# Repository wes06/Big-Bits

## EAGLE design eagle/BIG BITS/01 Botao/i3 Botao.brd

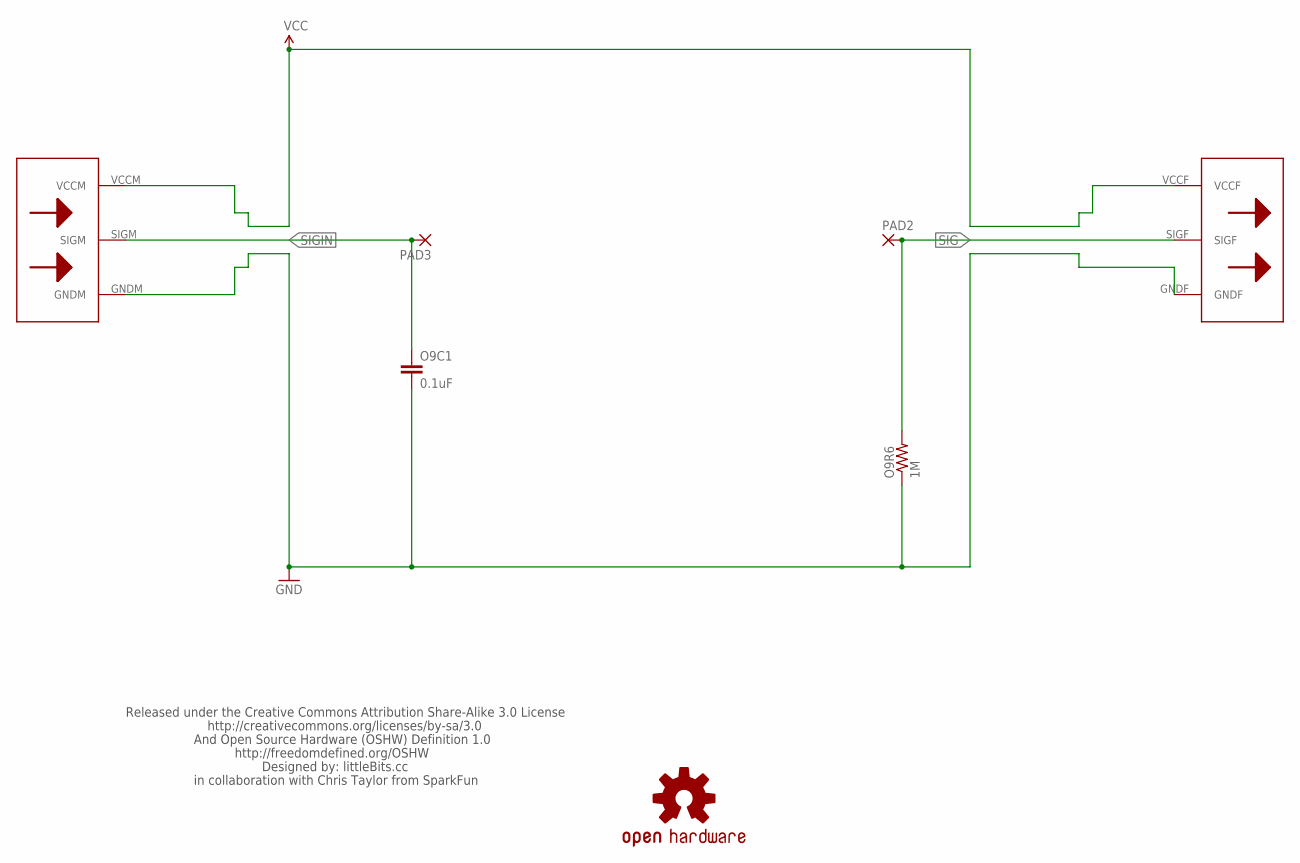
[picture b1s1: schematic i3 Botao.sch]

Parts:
O9C1: 0.1uF; 1206
O9R6: 1M; 0805
PAD2, PAD3: SMD5; SMD2,54-5,08
U$1: LB_CREDITS; OSHWCREDIT
U$2: BIGBIT
U$3: OSHW-LOGOL; OSHW-LOGO-L

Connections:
GND: O9C1.2, O9R6.1, U$2.GNDF, U$2.GNDM
SIG: O9R6.2, PAD2.1, U$2.SIGF
SIGIN: O9C1.1, PAD3.1, U$2.SIGM
VCC: U$2.VCCF, U$2.VCCM

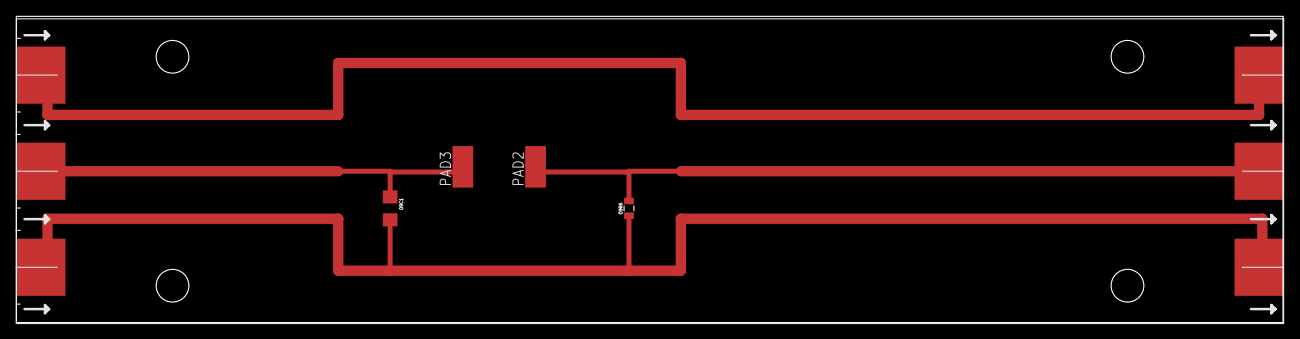
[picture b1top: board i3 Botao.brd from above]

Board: 2 copper layers, 154.9 x 37.5 mm, 7 parts (0 on the bottom side), 4 nets.

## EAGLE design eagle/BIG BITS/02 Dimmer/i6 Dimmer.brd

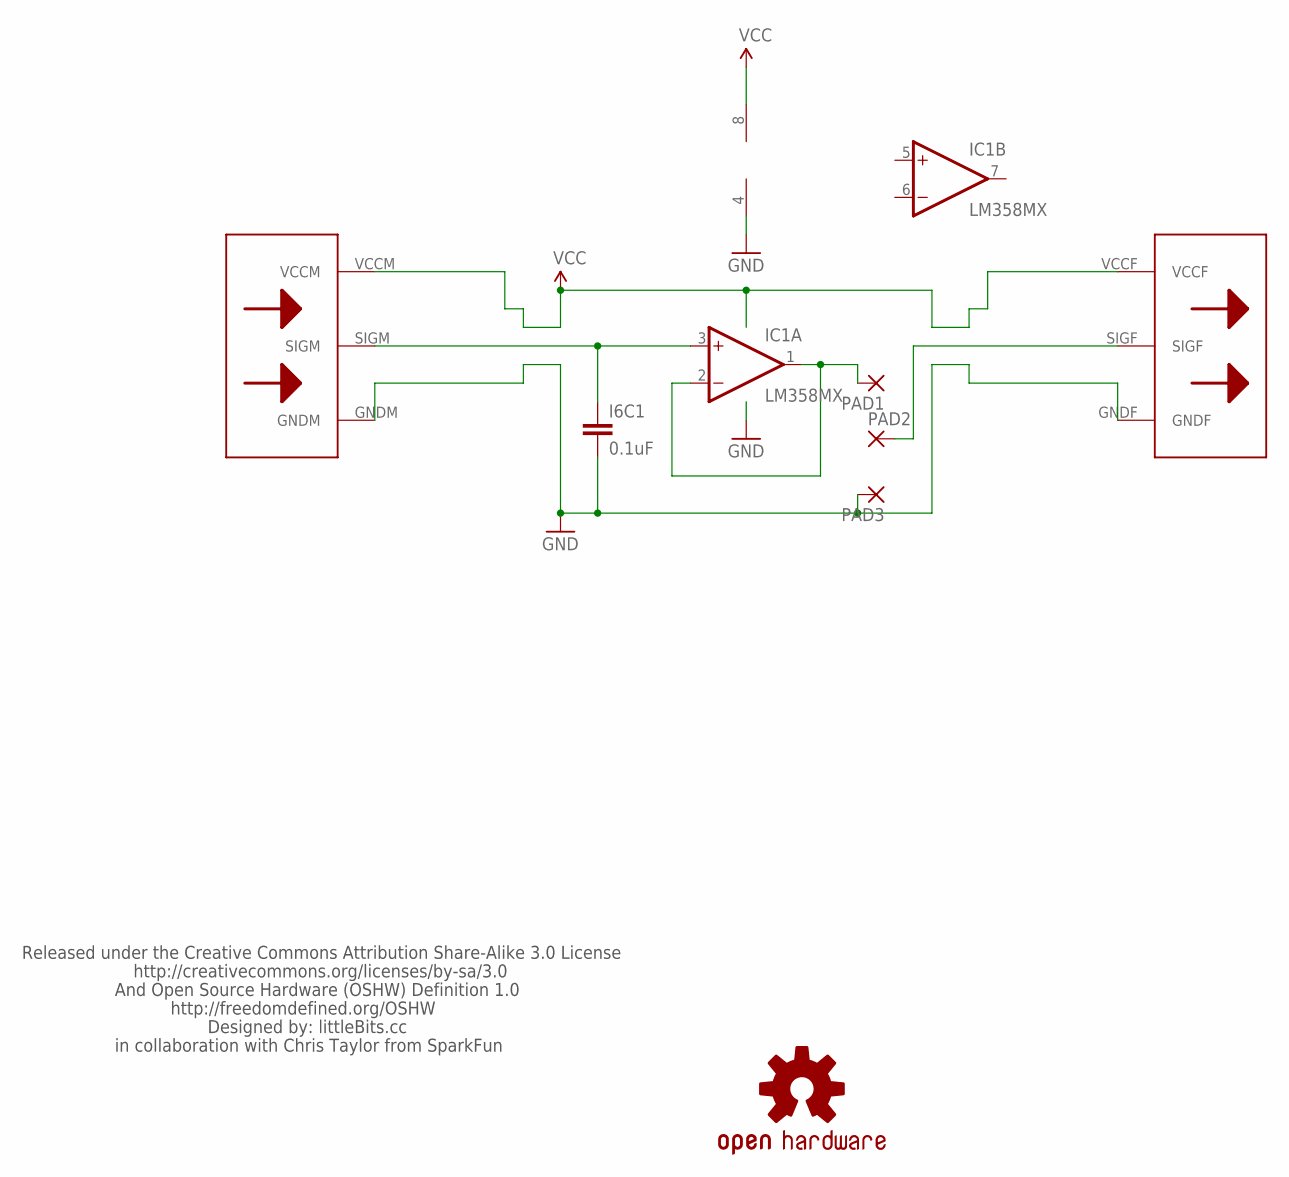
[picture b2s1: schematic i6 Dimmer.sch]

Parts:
I6C1: 0.1uF; 1206
IC1: LM358MX; SO08
PAD1, PAD2, PAD3: SMD5; SMD2,54-5,08
U$1: LB_CREDITS; OSHWCREDIT
U$3: OSHW-LOGOL; OSHW-LOGO-L
U$6: BIGBIT

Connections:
GND: I6C1.2, IC1.4 (V-), PAD3.1, U$6.GNDF, U$6.GNDM
unnamed: IC1.1 (OUT), IC1.2 (-IN), PAD1.1
POT: PAD2.1, U$6.SIGF
SIG: I6C1.1, IC1.3 (+IN), U$6.SIGM
VCC: IC1.8 (V+), U$6.VCCF, U$6.VCCM

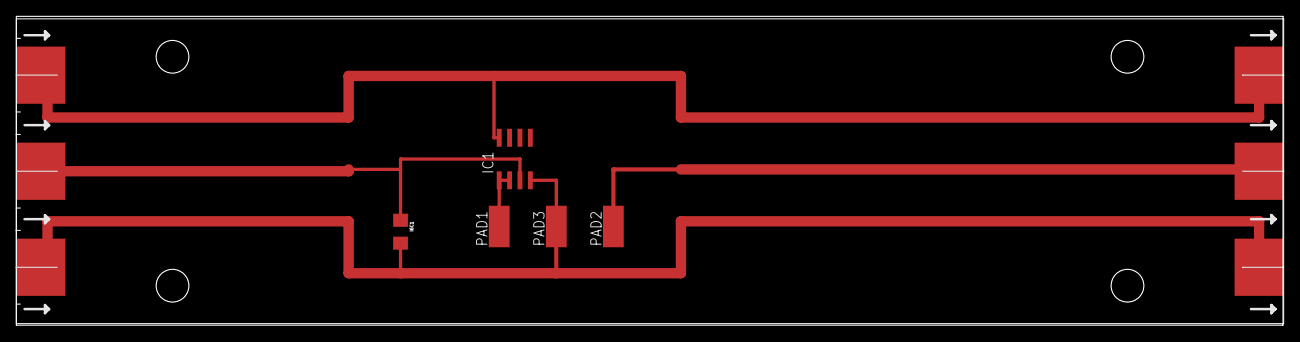
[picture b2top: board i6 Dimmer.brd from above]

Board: 2 copper layers, 154.9 x 37.8 mm, 8 parts (0 on the bottom side), 5 nets.

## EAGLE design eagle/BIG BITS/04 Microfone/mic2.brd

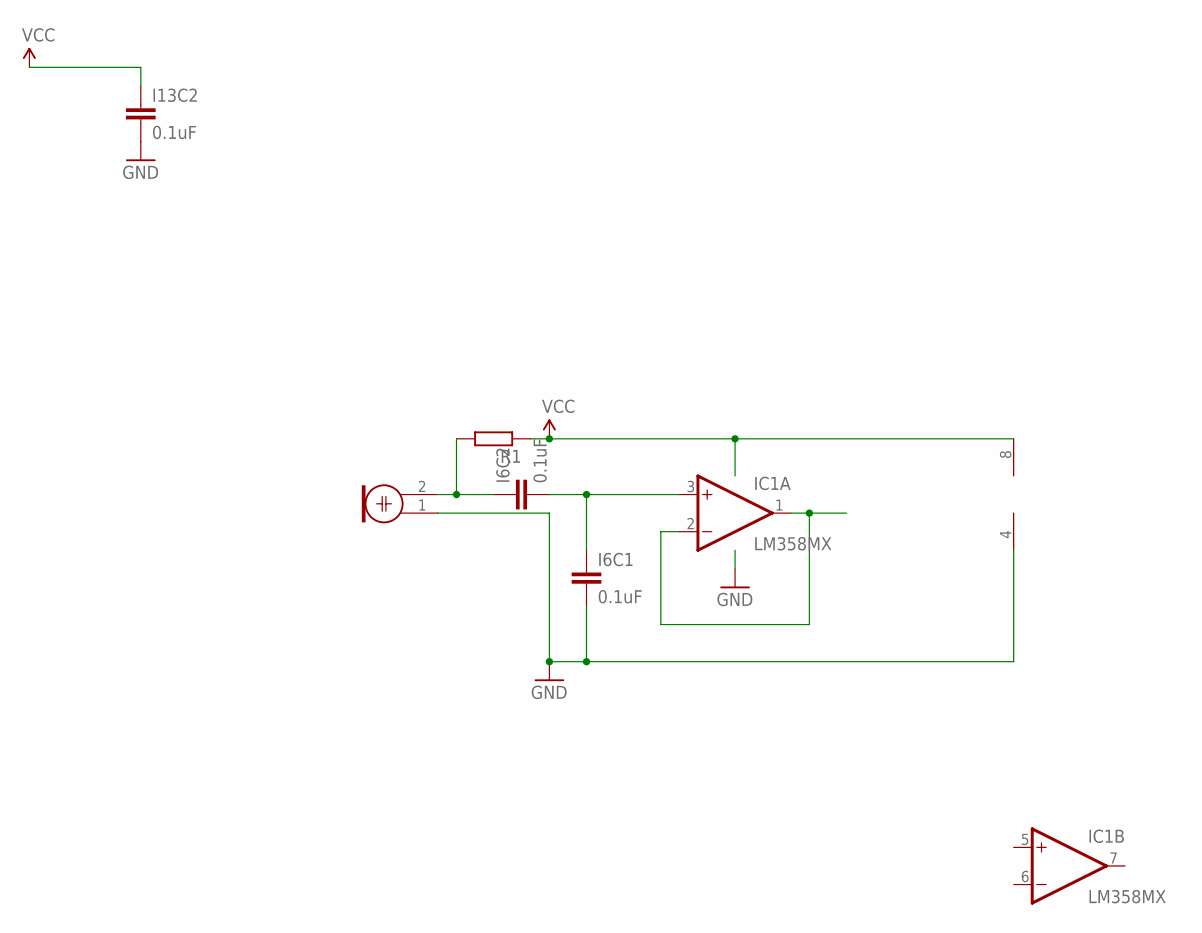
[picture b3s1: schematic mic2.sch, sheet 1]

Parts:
I6C1, I6C2, I13C2: 0.1uF; 1206
IC1: LM358MX; SO08
M1: ELECTRET_MICROPHON-WM-61A; WM-61A
R1: R-EU_M0805; M0805

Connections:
BLA: I6C1.1, I6C2.2, IC1.3 (+IN)
GND: I6C1.2, I13C2.2, IC1.4 (V-), M1.1; also elsewhere on the board
unnamed: I6C2.1, M1.2, R1.2
SIG: IC1.1 (OUT), IC1.2 (-IN)
VCC: I13C2.1, IC1.8 (V+), R1.1; also elsewhere on the board

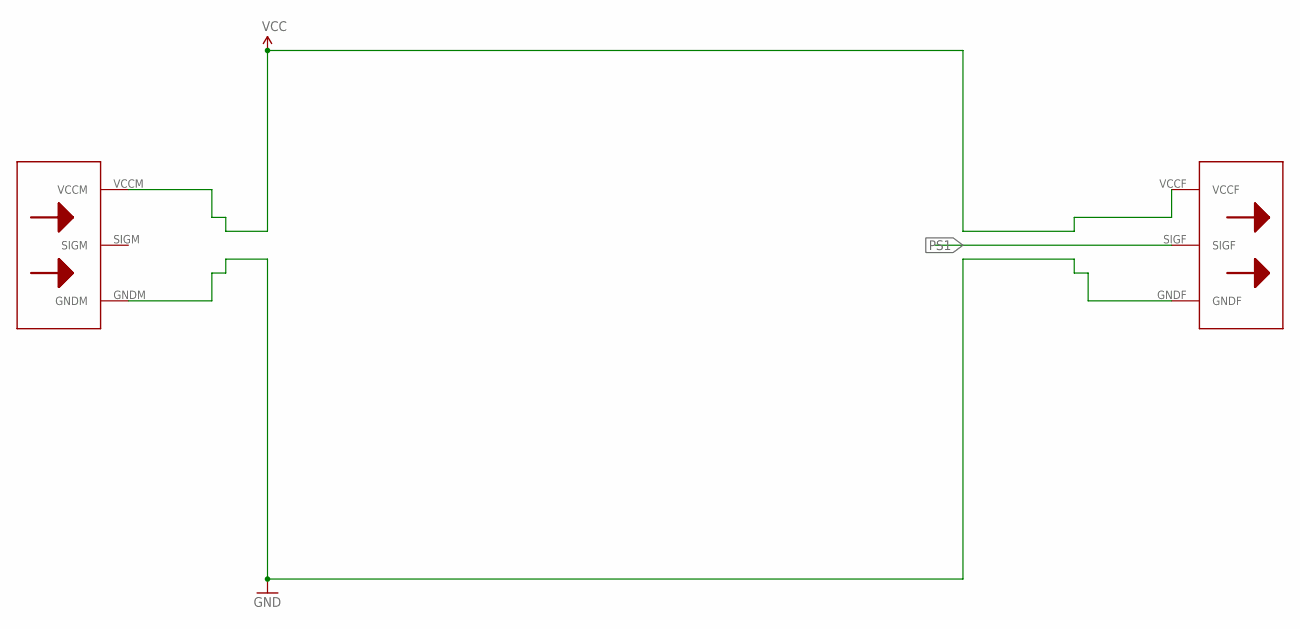
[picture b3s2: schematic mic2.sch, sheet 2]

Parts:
U$3: BIGBIT

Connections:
GND: U$3.GNDF, U$3.GNDM; also elsewhere on the board
PS1: U$3.SIGF
VCC: U$3.VCCF, U$3.VCCM; also elsewhere on the board

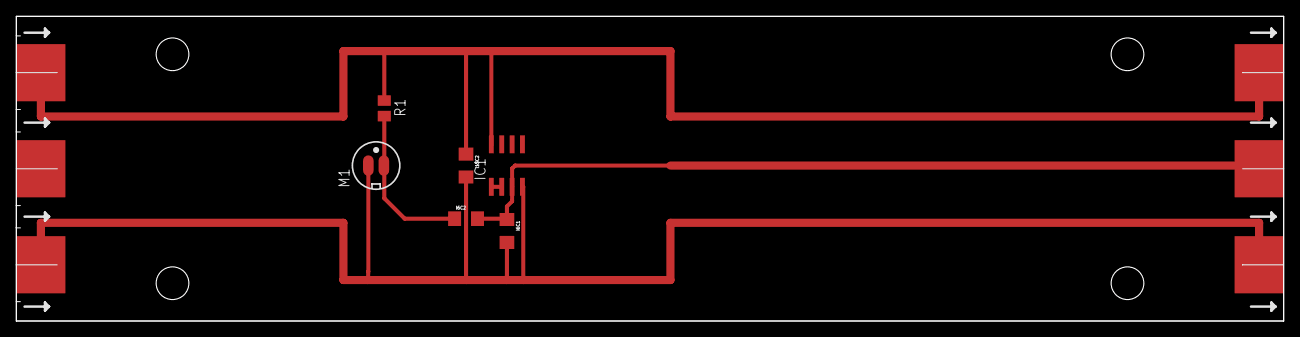
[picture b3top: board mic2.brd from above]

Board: 2 copper layers, 155.0 x 37.2 mm, 7 parts (0 on the bottom side), 5 nets.

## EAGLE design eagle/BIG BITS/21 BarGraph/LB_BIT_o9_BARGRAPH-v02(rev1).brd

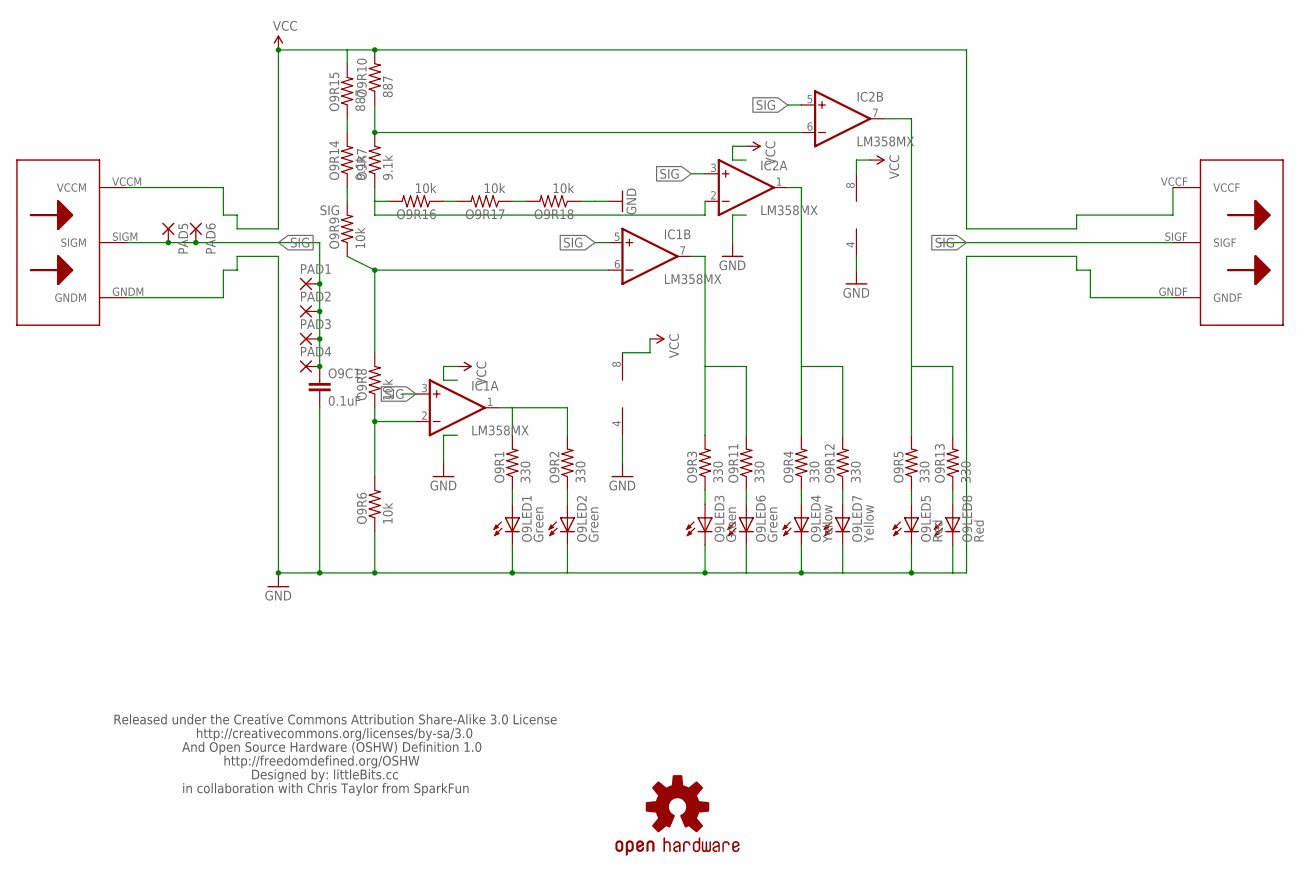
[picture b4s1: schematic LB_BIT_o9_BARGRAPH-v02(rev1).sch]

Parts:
IC1, IC2: LM358MX; SO08
O9C1: 0.1uF; 0603-CAP
O9LED1, O9LED2, O9LED3, O9LED6: Green; LED-1206
O9LED4, O9LED7: Yellow; LED-1206
O9LED5, O9LED8: Red; LED-1206
O9R1, O9R2, O9R3, O9R4, O9R5, O9R11, O9R12, O9R13: 330; 0805
O9R6, O9R8, O9R9, O9R16, O9R17, O9R18: 10k; 0805
O9R7, O9R14: 9.1k; 0805
O9R10, O9R15: 887; 0805
PAD1, PAD2, PAD3, PAD4, PAD5, PAD6: SMD2; SMD1,27-2,54
U$1: LB_CREDITS; OSHWCREDIT
U$3: OSHW-LOGOL; OSHW-LOGO-L
U$7: BIGBIT

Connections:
GND: IC1.4 (V-), IC2.4 (V-), O9C1.2, O9LED1.C, O9LED2.C, O9LED3.C, O9LED4.C, O9LED5.C, O9LED6.C, O9LED7.C, O9LED8.C, O9R6.1, O9R18.1, U$7.GNDF, U$7.GNDM
unnamed: IC1.1 (OUT), O9R1.2, O9R2.2
unnamed: O9LED1.A, O9R1.1
unnamed: O9R14.2, O9R15.1
unnamed: O9LED3.A, O9R3.1
unnamed: O9LED4.A, O9R4.1
unnamed: O9LED5.A, O9R5.1
unnamed: O9LED8.A, O9R13.1
unnamed: O9R9.2, O9R14.1
unnamed: O9LED7.A, O9R12.1
unnamed: O9LED6.A, O9R11.1
unnamed: IC1.7 (OUT), O9R3.2, O9R11.2
unnamed: IC2.1 (OUT), O9R4.2, O9R12.2
unnamed: IC2.7 (OUT), O9R5.2, O9R13.2
unnamed: IC1.2 (-IN), O9R6.2, O9R8.1
unnamed: IC2.2 (-IN), O9R7.1, O9R16.2
unnamed: IC1.6 (-IN), O9R8.2, O9R9.1
unnamed: O9R16.1, O9R17.2
unnamed: O9R17.1, O9R18.2
unnamed: O9LED2.A, O9R2.1
unnamed: IC2.6 (-IN), O9R7.2, O9R10.1
SIG: IC1.3 (+IN), IC1.5 (+IN), IC2.3 (+IN), IC2.5 (+IN), O9C1.1, PAD1.1, PAD2.1, PAD3.1, PAD4.1, PAD5.1, PAD6.1, U$7.SIGF, U$7.SIGM
VCC: IC1.8 (V+), IC2.8 (V+), O9R10.2, O9R15.2, U$7.VCCF, U$7.VCCM

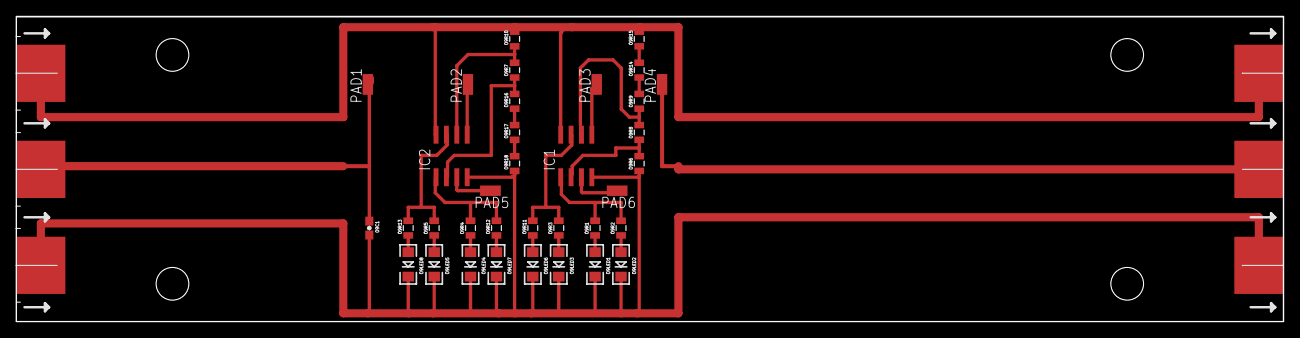
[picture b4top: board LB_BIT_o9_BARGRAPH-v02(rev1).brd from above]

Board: 2 copper layers, 155.0 x 37.3 mm, 38 parts (0 on the bottom side), 23 nets.

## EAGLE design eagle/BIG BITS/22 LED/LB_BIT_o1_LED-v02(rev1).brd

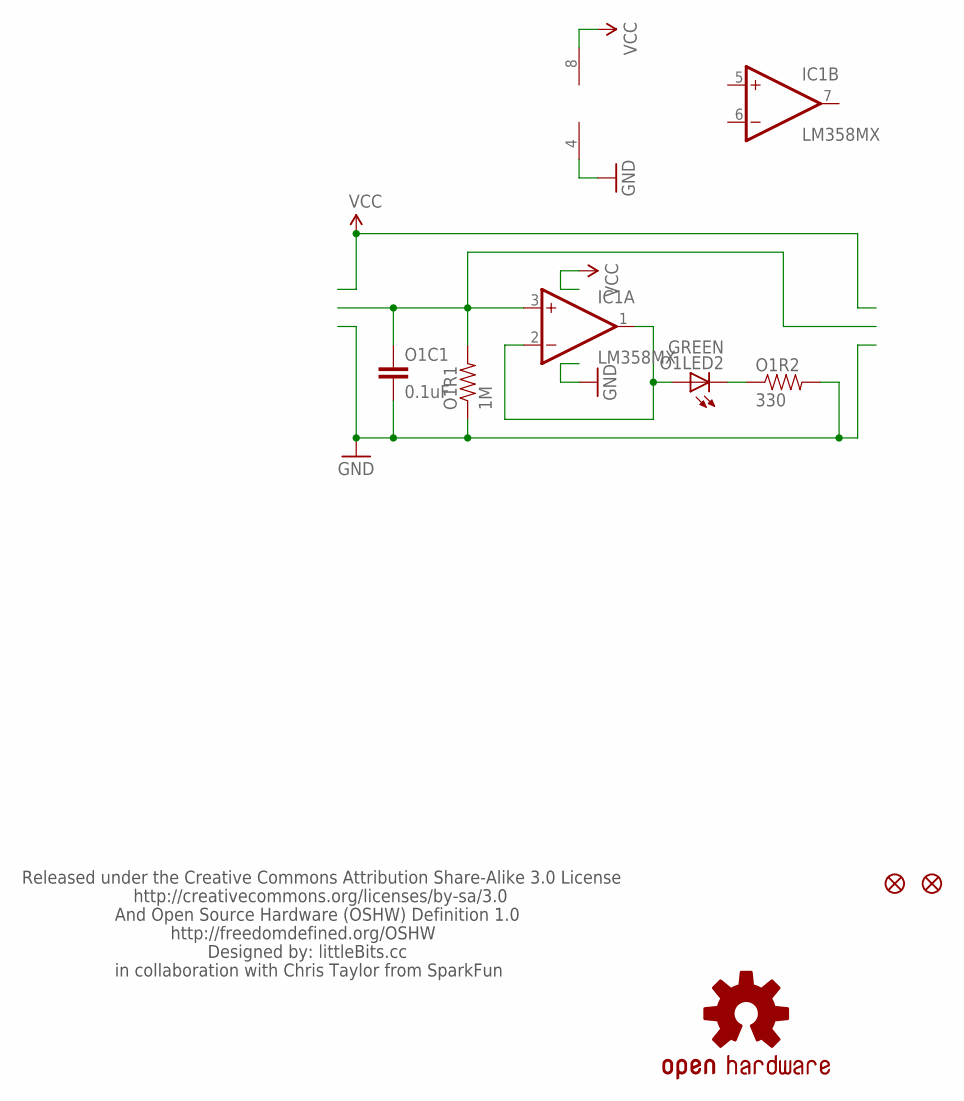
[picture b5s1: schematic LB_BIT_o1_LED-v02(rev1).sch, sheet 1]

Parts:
IC1: LM358MX; SO08
JP1, JP2: FIDUCIAL1X2.5; FIDUCIAL-1X2.5
O1C1: 0.1uF; 1206
O1LED2: GREEN; LED-1206
O1R1: 1M; 0805
O1R2: 330; 0805
U$1: LB_CREDITS; OSHWCREDIT
U$3: OSHW-LOGOL; OSHW-LOGO-L

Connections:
GND: IC1.4 (V-), O1C1.2, O1R1.1, O1R2.2; also elsewhere on the board
LEDGND: O1LED2.C, O1R2.1
unnamed: IC1.1 (OUT), IC1.2 (-IN), O1LED2.A
SIG: IC1.3 (+IN), O1C1.1, O1R1.2; also elsewhere on the board
VCC: IC1.8 (V+); also elsewhere on the board

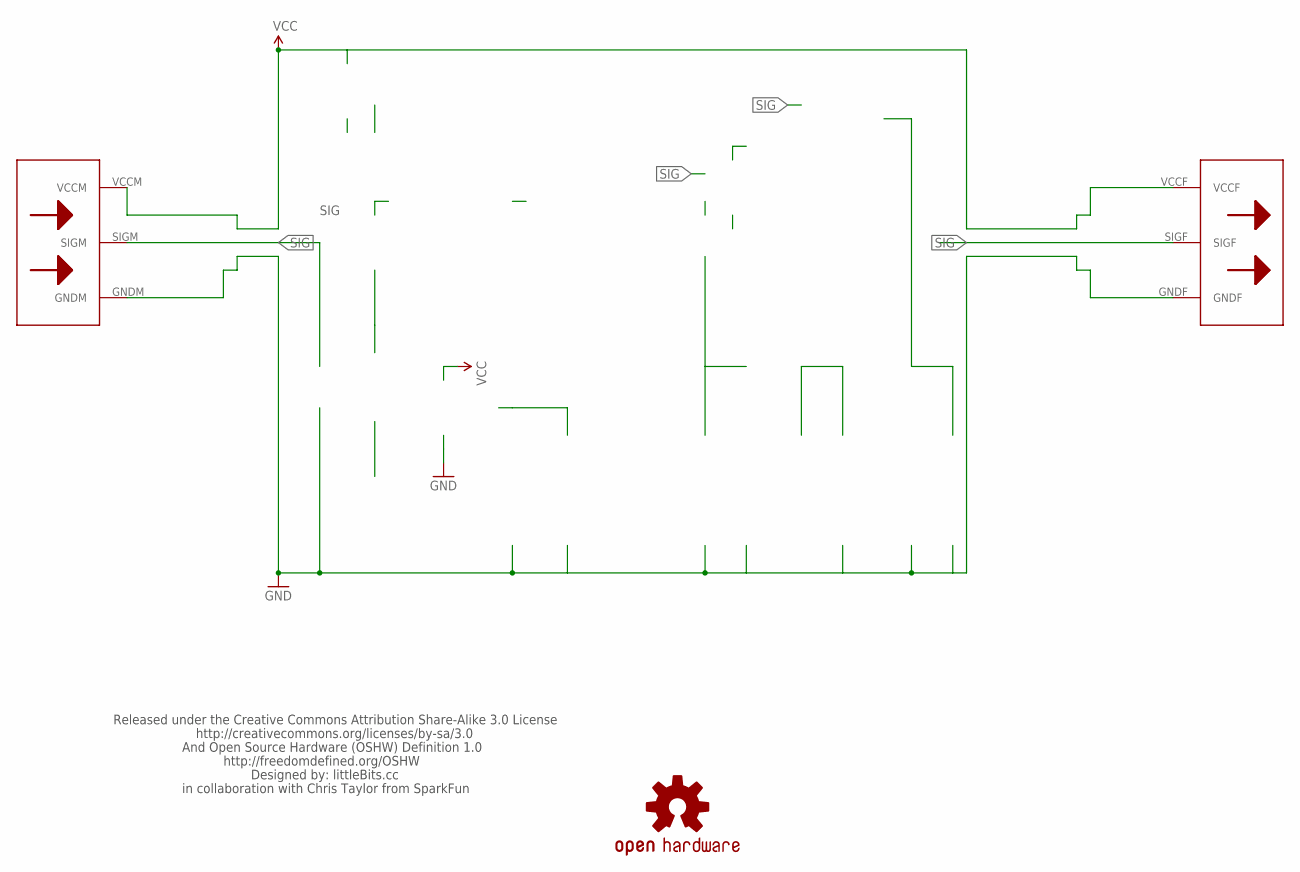
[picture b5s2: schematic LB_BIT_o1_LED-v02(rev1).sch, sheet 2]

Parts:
U$2: OSHW-LOGOL; OSHW-LOGO-L
U$4: LB_CREDITS; OSHWCREDIT
U$8: BIGBIT

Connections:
GND: U$8.GNDF, U$8.GNDM; also elsewhere on the board
SIG: U$8.SIGF, U$8.SIGM; also elsewhere on the board
VCC: U$8.VCCF, U$8.VCCM; also elsewhere on the board

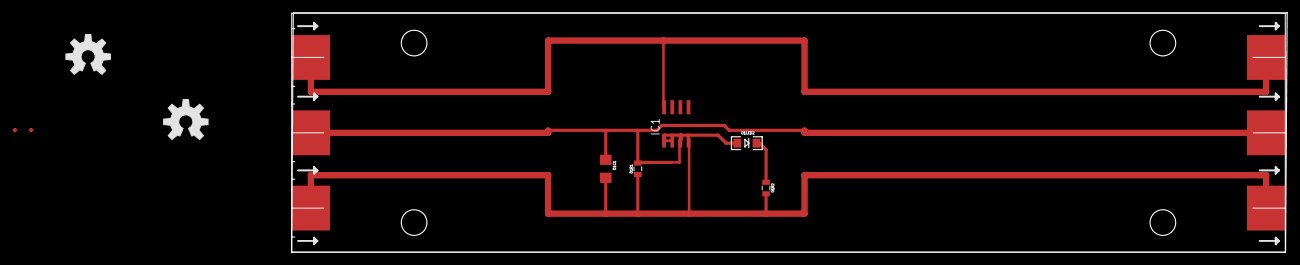
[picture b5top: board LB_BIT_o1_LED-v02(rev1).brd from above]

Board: 2 copper layers, 155.3 x 37.3 mm, 12 parts (0 on the bottom side), 5 nets.

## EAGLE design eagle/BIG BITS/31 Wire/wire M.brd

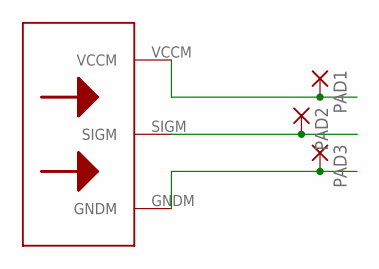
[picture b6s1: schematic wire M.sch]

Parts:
PAD1, PAD2, PAD3: SMD5; SMD2,54-5,08
U$2: BITWIREM

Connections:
unnamed: PAD1.1, U$2.VCCM
unnamed: PAD2.1, U$2.SIGM
unnamed: PAD3.1, U$2.GNDM

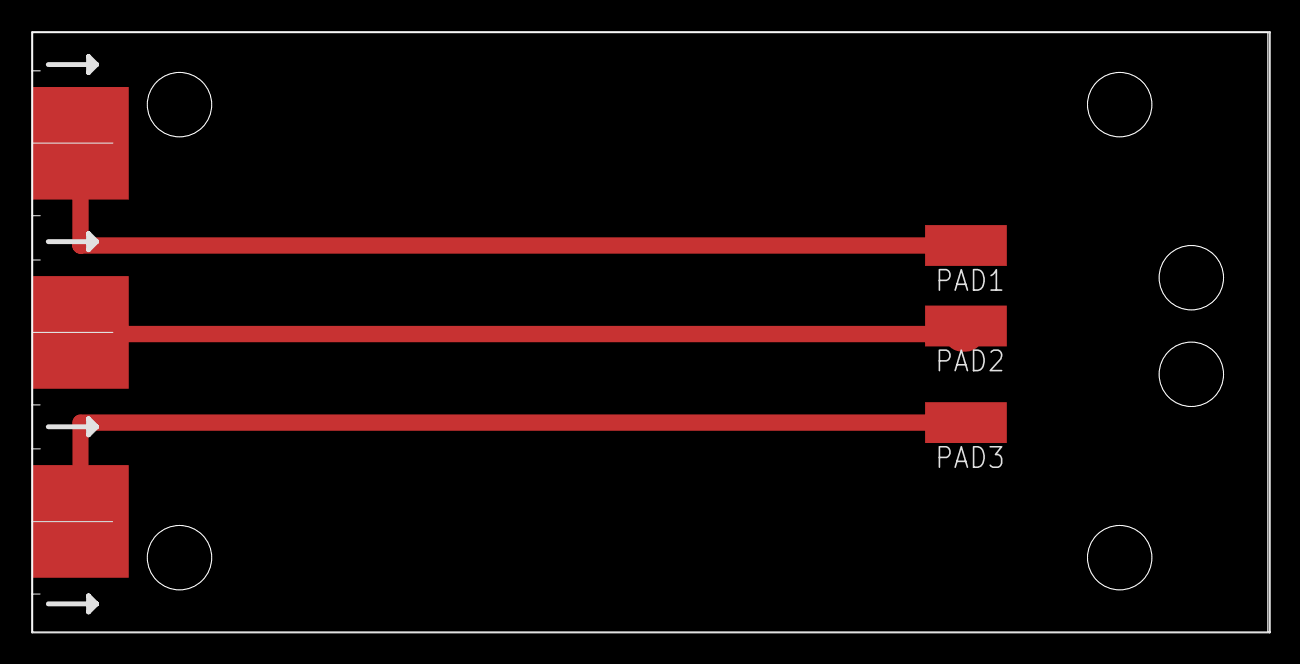
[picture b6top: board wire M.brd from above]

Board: 2 copper layers, 76.8 x 37.2 mm, 4 parts (0 on the bottom side), 3 nets.

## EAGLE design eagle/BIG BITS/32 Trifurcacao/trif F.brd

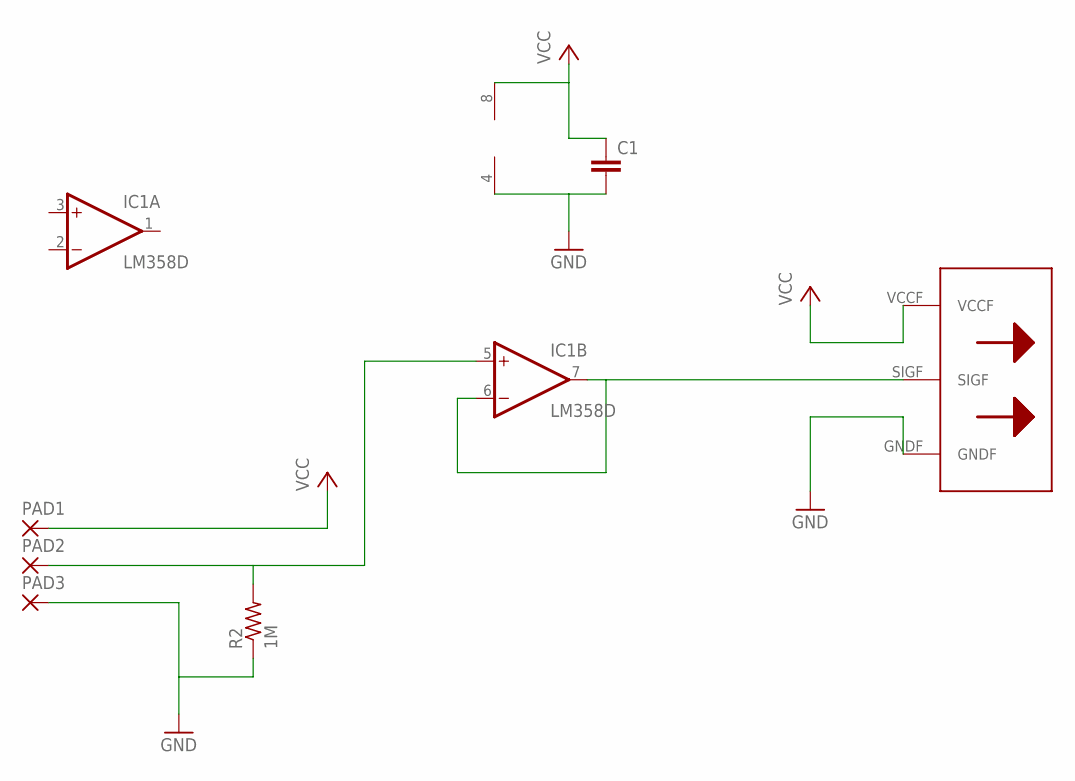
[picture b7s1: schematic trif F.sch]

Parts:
C1: C-EUC1206K; C1206K
IC1: LM358D; SO08
PAD1, PAD2, PAD3: SMD2; SMD1,27-2,54
R2: 1M; M0805
U$2: BITWIREF

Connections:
unnamed: IC1.6 (-IN), IC1.7 (OUT), U$2.SIGF
unnamed: C1.2, IC1.4 (V-), PAD3.1, R2.1, U$2.GNDF
SIG2: IC1.5 (+IN), PAD2.1, R2.2
VCC: C1.1, IC1.8 (V+), PAD1.1, U$2.VCCF

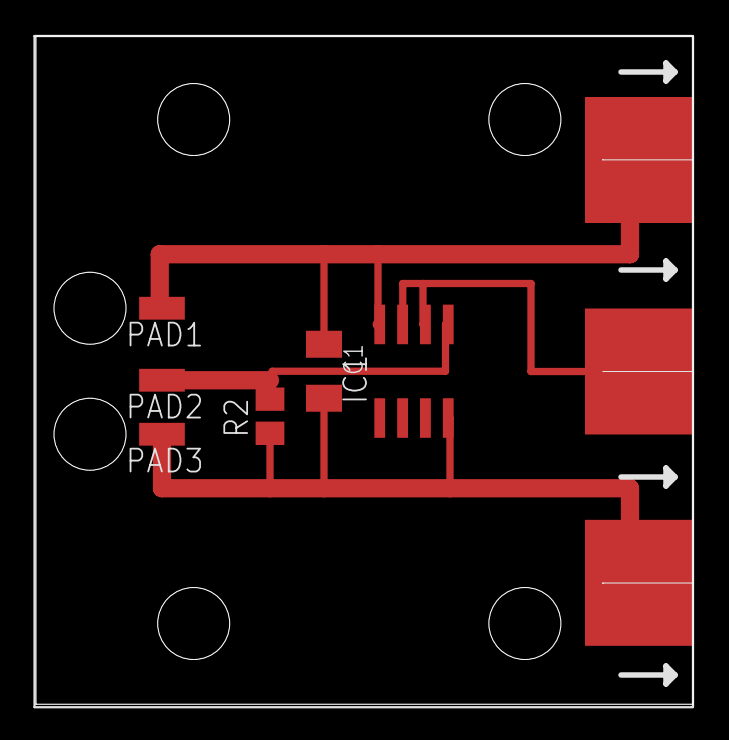
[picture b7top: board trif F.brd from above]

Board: 2 copper layers, 36.5 x 37.1 mm, 7 parts (0 on the bottom side), 4 nets.

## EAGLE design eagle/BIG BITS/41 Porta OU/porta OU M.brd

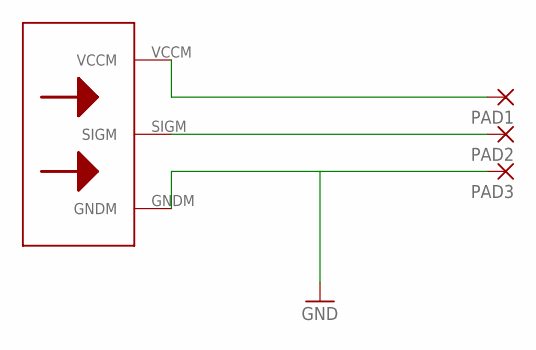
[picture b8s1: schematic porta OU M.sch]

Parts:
PAD1, PAD2, PAD3: SMD5; SMD2,54-5,08
U$1: BITWIREM

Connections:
GND: PAD3.1, U$1.GNDM
unnamed: PAD1.1, U$1.VCCM
SIG2: PAD2.1, U$1.SIGM

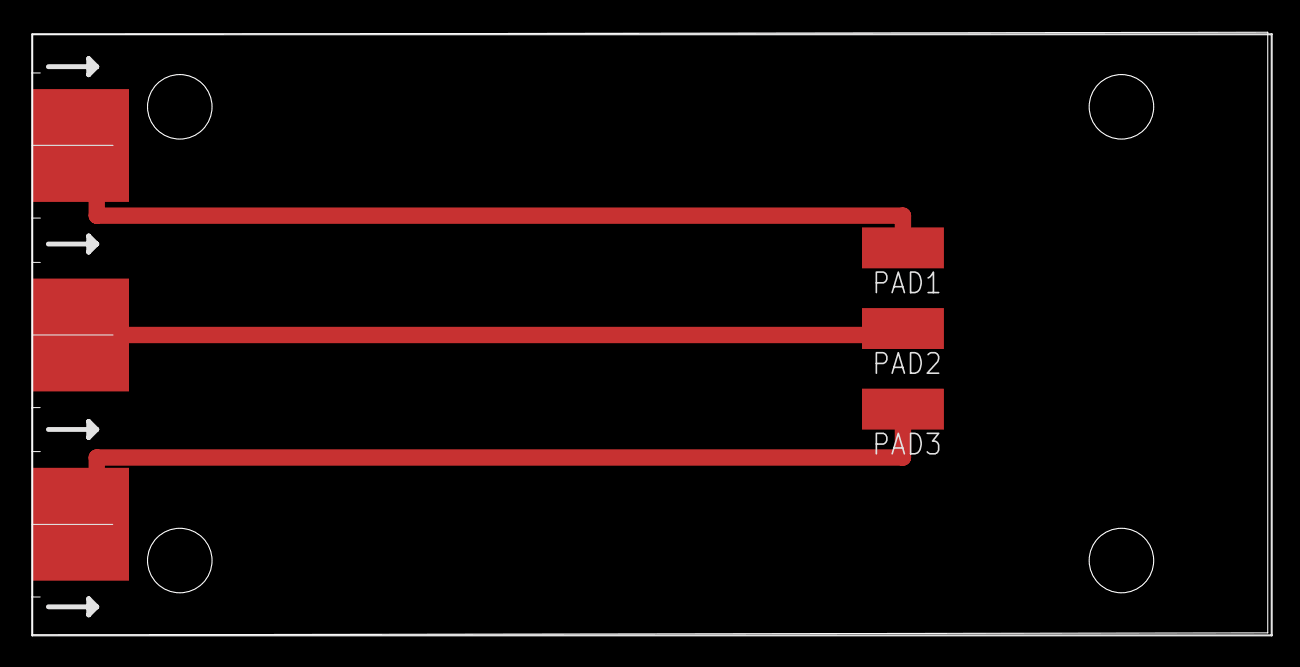
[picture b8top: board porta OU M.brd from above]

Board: 2 copper layers, 76.6 x 37.4 mm, 4 parts (0 on the bottom side), 3 nets.

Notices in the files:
parts and their libraries:
LITTLEBITS: Released under the Creative Commons Attribution Share-Alike 3.0 License
LITTLEBITS: http://creativecommons.org/license/by-sa/3.0
LITTLEBITS: http://creativecommons.org/licenses/by-sa/3.0
